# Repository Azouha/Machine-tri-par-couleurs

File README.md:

# Machine-tri-par-couleurs
Partie électronique (schématiques, PCB...) + partie programmation,
prochainement je vais faire une caméra au lieu de capteur des coleur est 
traiter les images avec une unité plus puissante que ATEMGA par exemple 
Raspberry .

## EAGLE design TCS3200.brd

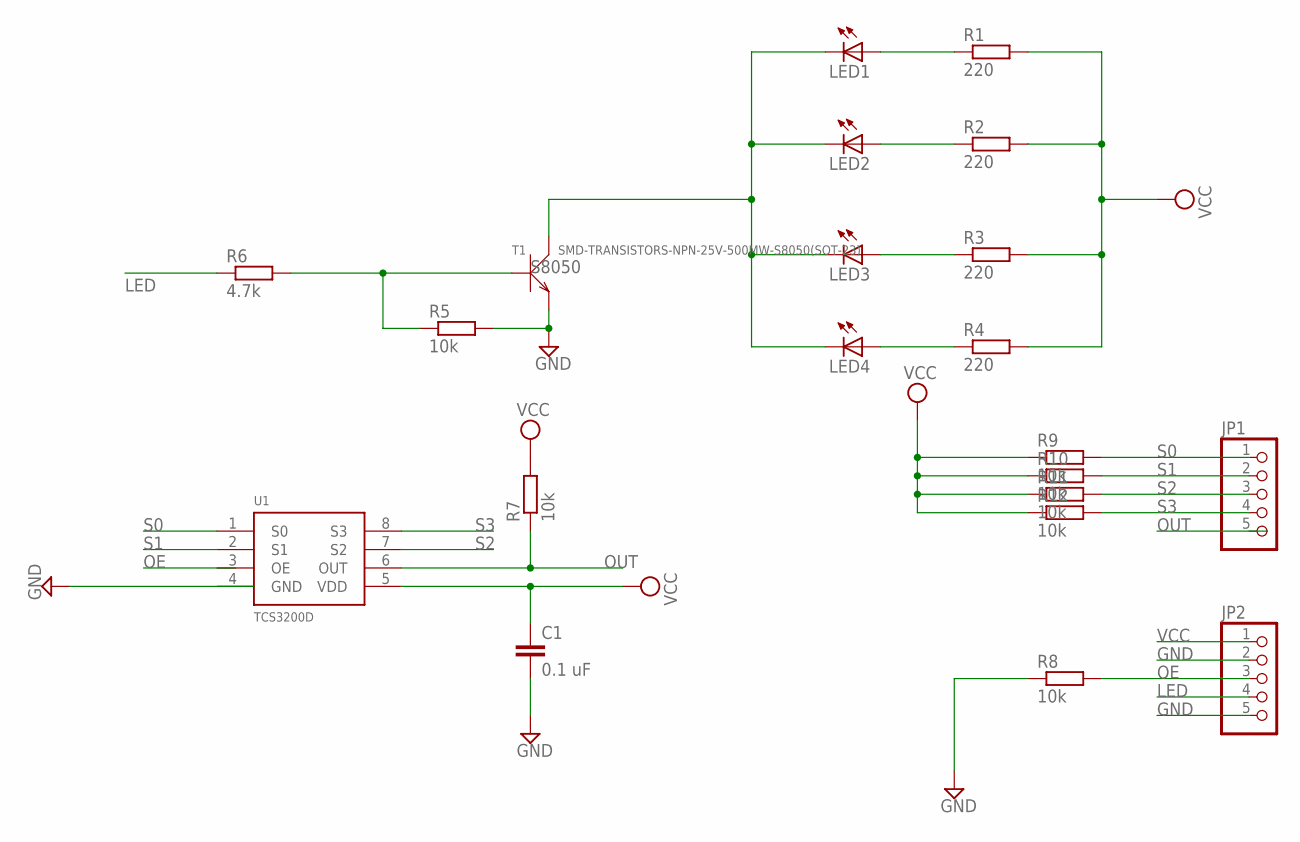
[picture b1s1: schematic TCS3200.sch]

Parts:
C1: 0.1 uF; C3216
JP1, JP2: PINHD-1X5/90; 1X05/90
LED1, LED2, LED3, LED4: LEDSML1206; SML1206
R1, R2, R3, R4: 220; R2012W
R5, R7, R8, R9, R10, R11, R12: 10k; R2012W
R6: 4.7k; R2012W
T1: SMD-TRANSISTORS-NPN-25V-500MW-S8050(SOT-23); SOT-23
U1: TCS3200D; SOIC8

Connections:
GND: C1.2, JP2.2, JP2.5, R5.2, R8.1, T1.2 (E)
LED: JP2.4, R6.1
unnamed: LED1.A, R1.1
unnamed: LED2.A, R2.1
unnamed: LED3.A, R3.1
unnamed: LED4.A, R4.1
unnamed: LED1.C, LED2.C, LED3.C, LED4.C, T1.3 (C)
unnamed: R5.1, R6.2, T1.1 (B)
OE: JP2.3, R8.2
OUT: R7.1, U1.6 (OUT)
S0: JP1.1, R9.2, U1.1 (S0)
S1: JP1.2, R10.2
S2: JP1.3, R11.2, U1.7 (S2)
S3: JP1.4, R12.2, U1.8 (S3)
VCC: C1.1, JP2.1, R1.2, R2.2, R3.2, R4.2, R7.2, R9.1, R10.1, R11.1, R12.1, U1.5 (VDD)

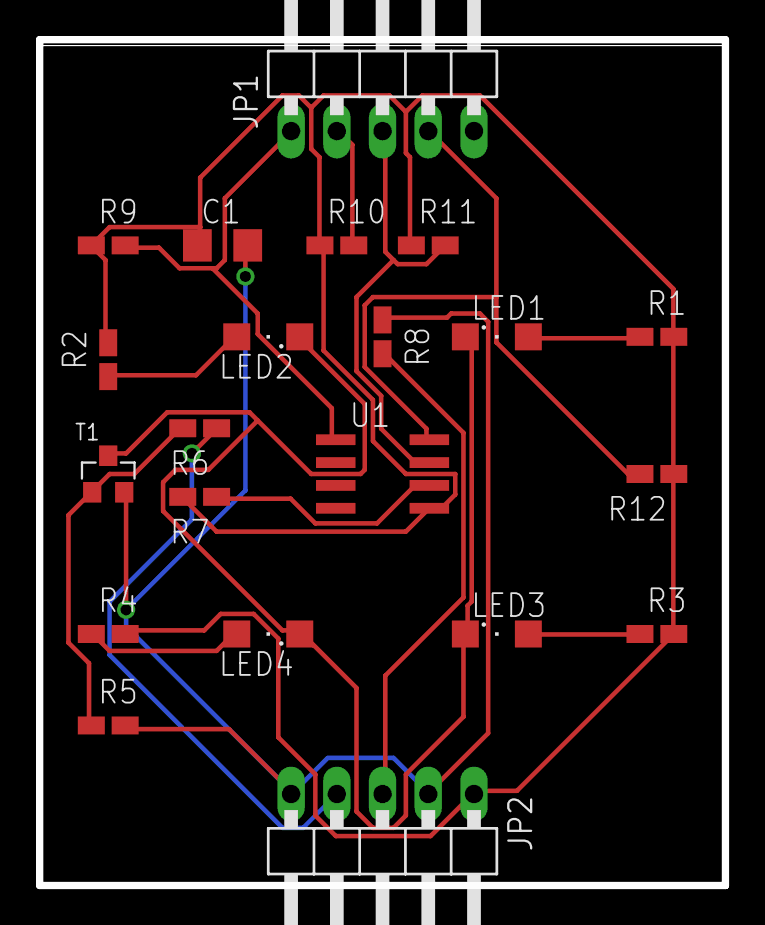
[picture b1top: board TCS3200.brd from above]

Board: 2 copper layers, 38.1 x 47.0 mm, 21 parts (0 on the bottom side), 15 nets.

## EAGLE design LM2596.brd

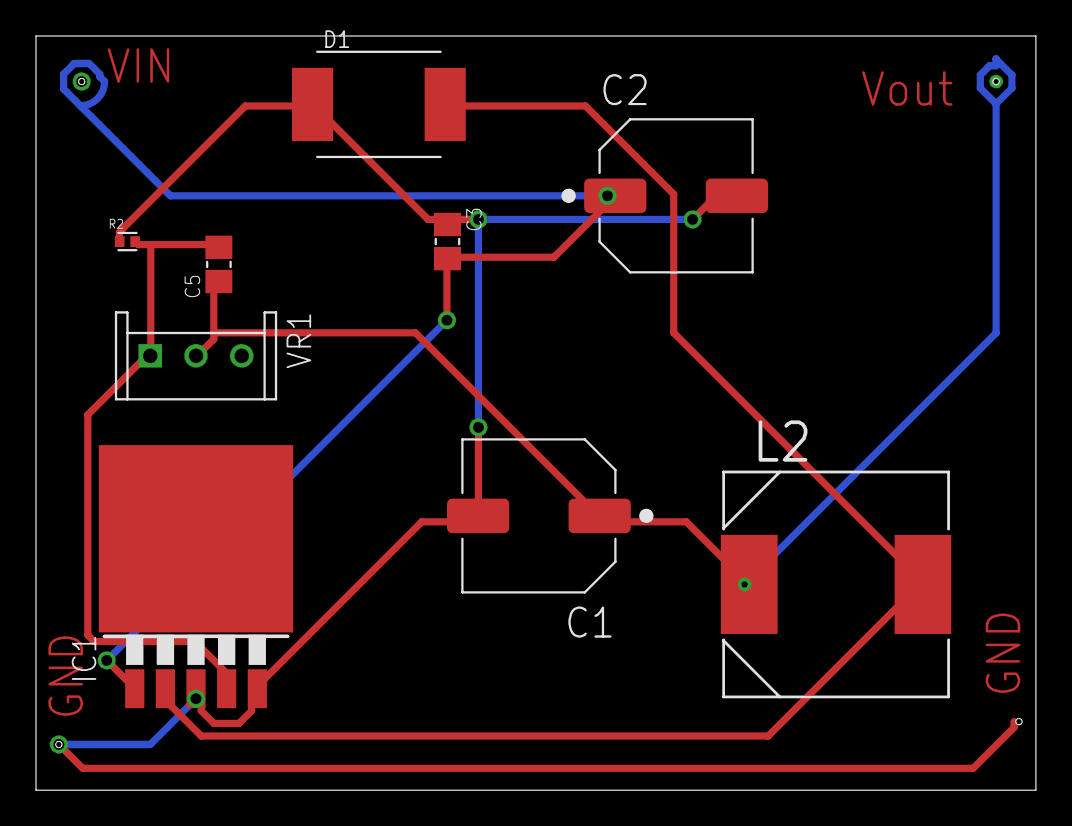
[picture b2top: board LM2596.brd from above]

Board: 2 copper layers, 55.6 x 41.9 mm, 9 parts (0 on the bottom side), 5 nets.

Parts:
C1, C2: PCR1C221MCL1GS; CAPE830X690N
C3, C5: GRM219F51H104ZA01D; CAPC2012X135N
D1: SMD-DIODE-SCHOTTKY-40V-3A(DO-214AB); DO-214AB
IC1: LM2596S; TO263-5
L2: DR125-331-R; INDM125125X600N
R2: CH0402-330RGFPT; RESC1005X40
VR1: W

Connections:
GND: C1.2, C2.2, C3.1, D1.1, IC1.3, IC1.5, R2.1
unnamed: D1.2, IC1.2, L2.2
unnamed: C5.2, IC1.4, R2.2, VR1.1
VIN: C2.1, C3.2, IC1.1
VOUT: C1.1, C5.1, L2.1, VR1.2

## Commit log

2019-02-14 le programme
2019-02-14 inshaelh

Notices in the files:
parts and their libraries:
3296W: Creative Commons Attribution-ShareAlike 3.0 Unported (CC BY-SA 3.0), http://creativecommons.org/licenses/by-sa/3.0/.
